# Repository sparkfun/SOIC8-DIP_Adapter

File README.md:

SparkFun SOIC8 to DIP Adapter -8 Pin
====================================

[*SparkFun SOIC to DIP Adapter 8-pin(BOB-00494)*](https://www.sparkfun.com/products/494)

This breakout board enables you to interface standard JEDEC SOIC devices to standard 0.1" headers. 

Repository Contents
-------------------
* **/Documentation** - Dimensional datasheets
* **/Hardware** - All Eagle design files (.brd, .sch)

License Information
-------------------

This product is _**open source**_! 

Please review the LICENSE.md file for license information. 

If you have any questions or concerns on licensing, please contact techsupport@sparkfun.com.

Distributed as-is; no warranty is given.

- Your friends at SparkFun.

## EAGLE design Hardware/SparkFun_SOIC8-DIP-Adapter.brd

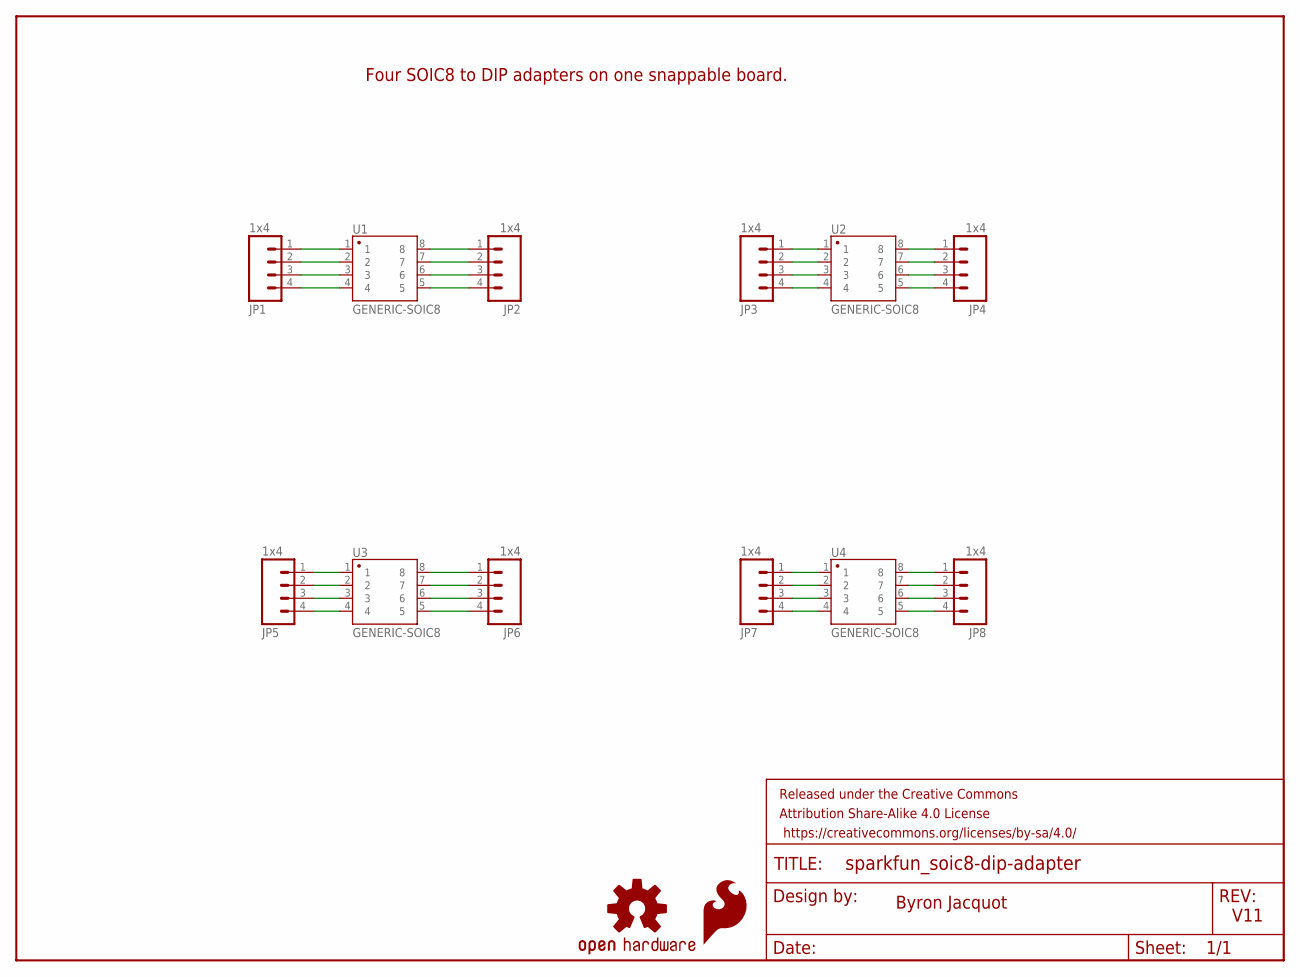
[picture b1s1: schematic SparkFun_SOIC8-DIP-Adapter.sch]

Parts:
FRAME1: frame; CREATIVE_COMMONS
JP1, JP3, JP5, JP7: 1x4; 1X04_NO_SILK
JP2, JP4, JP6, JP8: 1x4; 1X04_NO_SILK_ALL_ROUND
LOGO1: SFE_LOGO_FLAME.1_INCH; SFE_LOGO_FLAME_.1
LOGO2: OSHW-LOGOS; OSHW-LOGO-S
U1, U2, U3, U4: GENERIC-SOIC8; SO08-UNIVERSAL

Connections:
unnamed: JP1.1, U1.1
unnamed: JP1.2, U1.2
unnamed: JP1.3, U1.3
unnamed: JP1.4, U1.4
unnamed: JP2.1, U1.8
unnamed: JP2.2, U1.7
unnamed: JP2.3, U1.6
unnamed: JP2.4, U1.5
unnamed: JP3.1, U2.1
unnamed: JP3.2, U2.2
unnamed: JP3.3, U2.3
unnamed: JP3.4, U2.4
unnamed: JP4.1, U2.8
unnamed: JP4.2, U2.7
unnamed: JP4.3, U2.6
unnamed: JP4.4, U2.5
unnamed: JP5.1, U3.1
unnamed: JP5.2, U3.2
unnamed: JP5.3, U3.3
unnamed: JP5.4, U3.4
unnamed: JP6.4, U3.5
unnamed: JP6.3, U3.6
unnamed: JP6.2, U3.7
unnamed: JP6.1, U3.8
unnamed: JP7.1, U4.1
unnamed: JP7.2, U4.2
unnamed: JP7.3, U4.3
unnamed: JP7.4, U4.4
unnamed: JP8.1, U4.8
unnamed: JP8.2, U4.7
unnamed: JP8.3, U4.6
unnamed: JP8.4, U4.5

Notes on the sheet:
Byron Jacquot
V11
Four SOIC8 to DIP adapters on one snappable board.

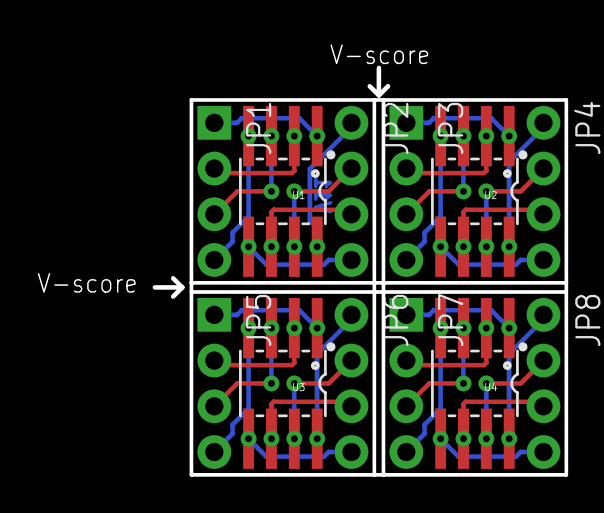
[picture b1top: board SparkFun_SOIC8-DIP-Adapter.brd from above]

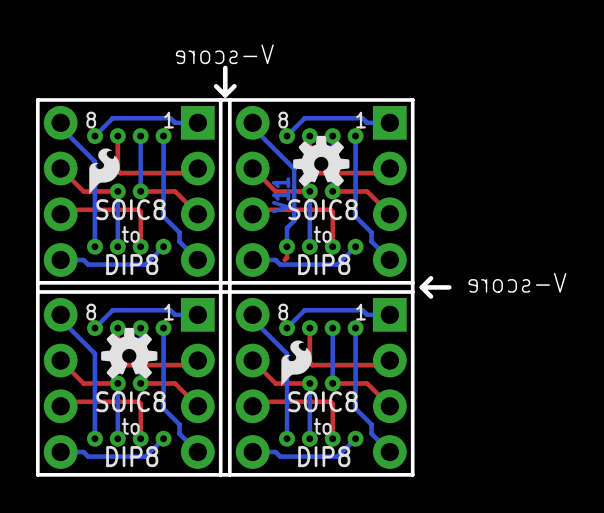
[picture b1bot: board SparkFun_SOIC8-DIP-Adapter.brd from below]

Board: 2 copper layers, 22.9 x 22.6 mm, 17 parts (4 on the bottom side), 32 nets.

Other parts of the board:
LOGO3: OSHW-LOGOS; OSHW-LOGO-S
LOGO4: SFE_LOGO_FLAME.1_INCH; SFE_LOGO_FLAME_.1@1

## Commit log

2015-01-05 Initial hardware file commit
2015-03-20 V11 Revision
    Several changes, addressing comments on old product:
    -Fit SOIC within DIP outline.
    -Longer SOIC pads to fit narrow & wide chips.
    -Vias in the SOIC pads to stake them down.
2015-03-20 Some small updates
2015-03-25 Updated after group review.
    -Fixed panelization.
    -Added DIP pin numbers to bottom silk.
    -Moved version # to top edge.
2015-03-25 Updated with Pete's revised logos
    To speed up CAM jobs.
2015-03-26 Checklist-related updates.
    Should handle all issues:
    -names/values were on wring layers
    -added dimension lines
2015-05-26 Updates after reviewing protos.
    Wider SOIC footprint.
    DIP pin 1 marked with square pad.
    Some rearrangement of silk elements.
2015-05-27 Fixing review issues
    * CC block location.
    * Ver # mismatch between schem and PCB.
2015-05-28 added simple text to dimension layer noting v-scores
2015-07-01 Moving version numbers back to V11, matching branch name.
2015-07-01 Fixing merge error.
    Something duplicated layer settings for 20, 21, 22.
2015-07-23 Adding files for annotated board & footprint dimensions
    As requested by Tech Support.
2015-08-24 Updating README, adding LICENSE file

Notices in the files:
parts and their libraries:
SparkFun-Aesthetics: Licensing: Creative Commons ShareAlike 4.0 International - https://creativecommons.org/licenses/by-sa/4.0
SparkFun-Aesthetics: Released under the Creative Commons Attribution Share-Alike 4.0 License
SparkFun-Aesthetics: https://creativecommons.org/licenses/by-sa/4.0
